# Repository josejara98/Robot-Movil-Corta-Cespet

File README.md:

# 🤖 Prototipo de Robot móvil Cortacésped

Este repositorio contiene el diseño de hardware y el firmware base para la unidad de control central de un robot móvil cortacésped teleoperado

El núcleo de este proyecto es una **PCB personalizada**  diseñada para gestionar potencia, navegación y sistema de seguridad utilizando el microcontrolador **ESP32-S3**.

## Especificaciones Técnicas de la PCB

Nuestra especialización se centra en la integración de sensores y la gestión de actuadores de potencia:

### Cerebro y Conectividad
* **MCU:** `ESP32-S3-WROOM-1`. Doble núcleo con soporte nativo para Wi-Fi y Bluetooth

### Sistema de Seguridad y Detección de Obstáculos
El robot implementa una estrategia de seguridad de dos niveles:
1.  **Nivel Preventivo (Ultrasonidos):** 3 sensores ultrasónicos estratégicamente posicionados para la detección de obstáculos a distancia
2.  **Nivel de Contacto (Bumpers):** 4 finales de carrera instalados en el chasis como "Bumpers". Funcionan como la última barrera física
* **Regulación:** `LDL1117S33R`. LDO de alta eficiencia para una alimentación estable de 3.3V.
* **Precisión de Batería:** `ADS1015LIDGSR`. ADC externo de 12 bits para un monitoreo crítico del voltaje

### Navegación y Movimiento
* **IMU:** `IIM-42652`. Sensor de 6 ejes de grado industrial para mantener el rumbo y detectar inclinaciones peligrosas.
* **Control de Tracción:** Pines de salida (Dupont) para conectar un **driver de motor DC externo** para el desplazamiento del robot.

### Sistema de Corte (Brushless)
La PCB cuenta con salidas específicas para controlar **3 ESC (Electronic Speed Controllers)** independientes:
* **2 Motores Brushless:** Dedicados al corte principal de césped.
* **1 Motor Brushless:** Dedicado a la función de bordeadora

### Interfaz de Usuario
* **Buzzer SMT:** `CMI-9705-0580-SMT-TR`. Notifica mediante códigos acústicos:
    * **Movimiento inminente:** Alerta antes de activar cuchillas o tracción.
    * **Batería Baja:** Alerta de retorno a base.

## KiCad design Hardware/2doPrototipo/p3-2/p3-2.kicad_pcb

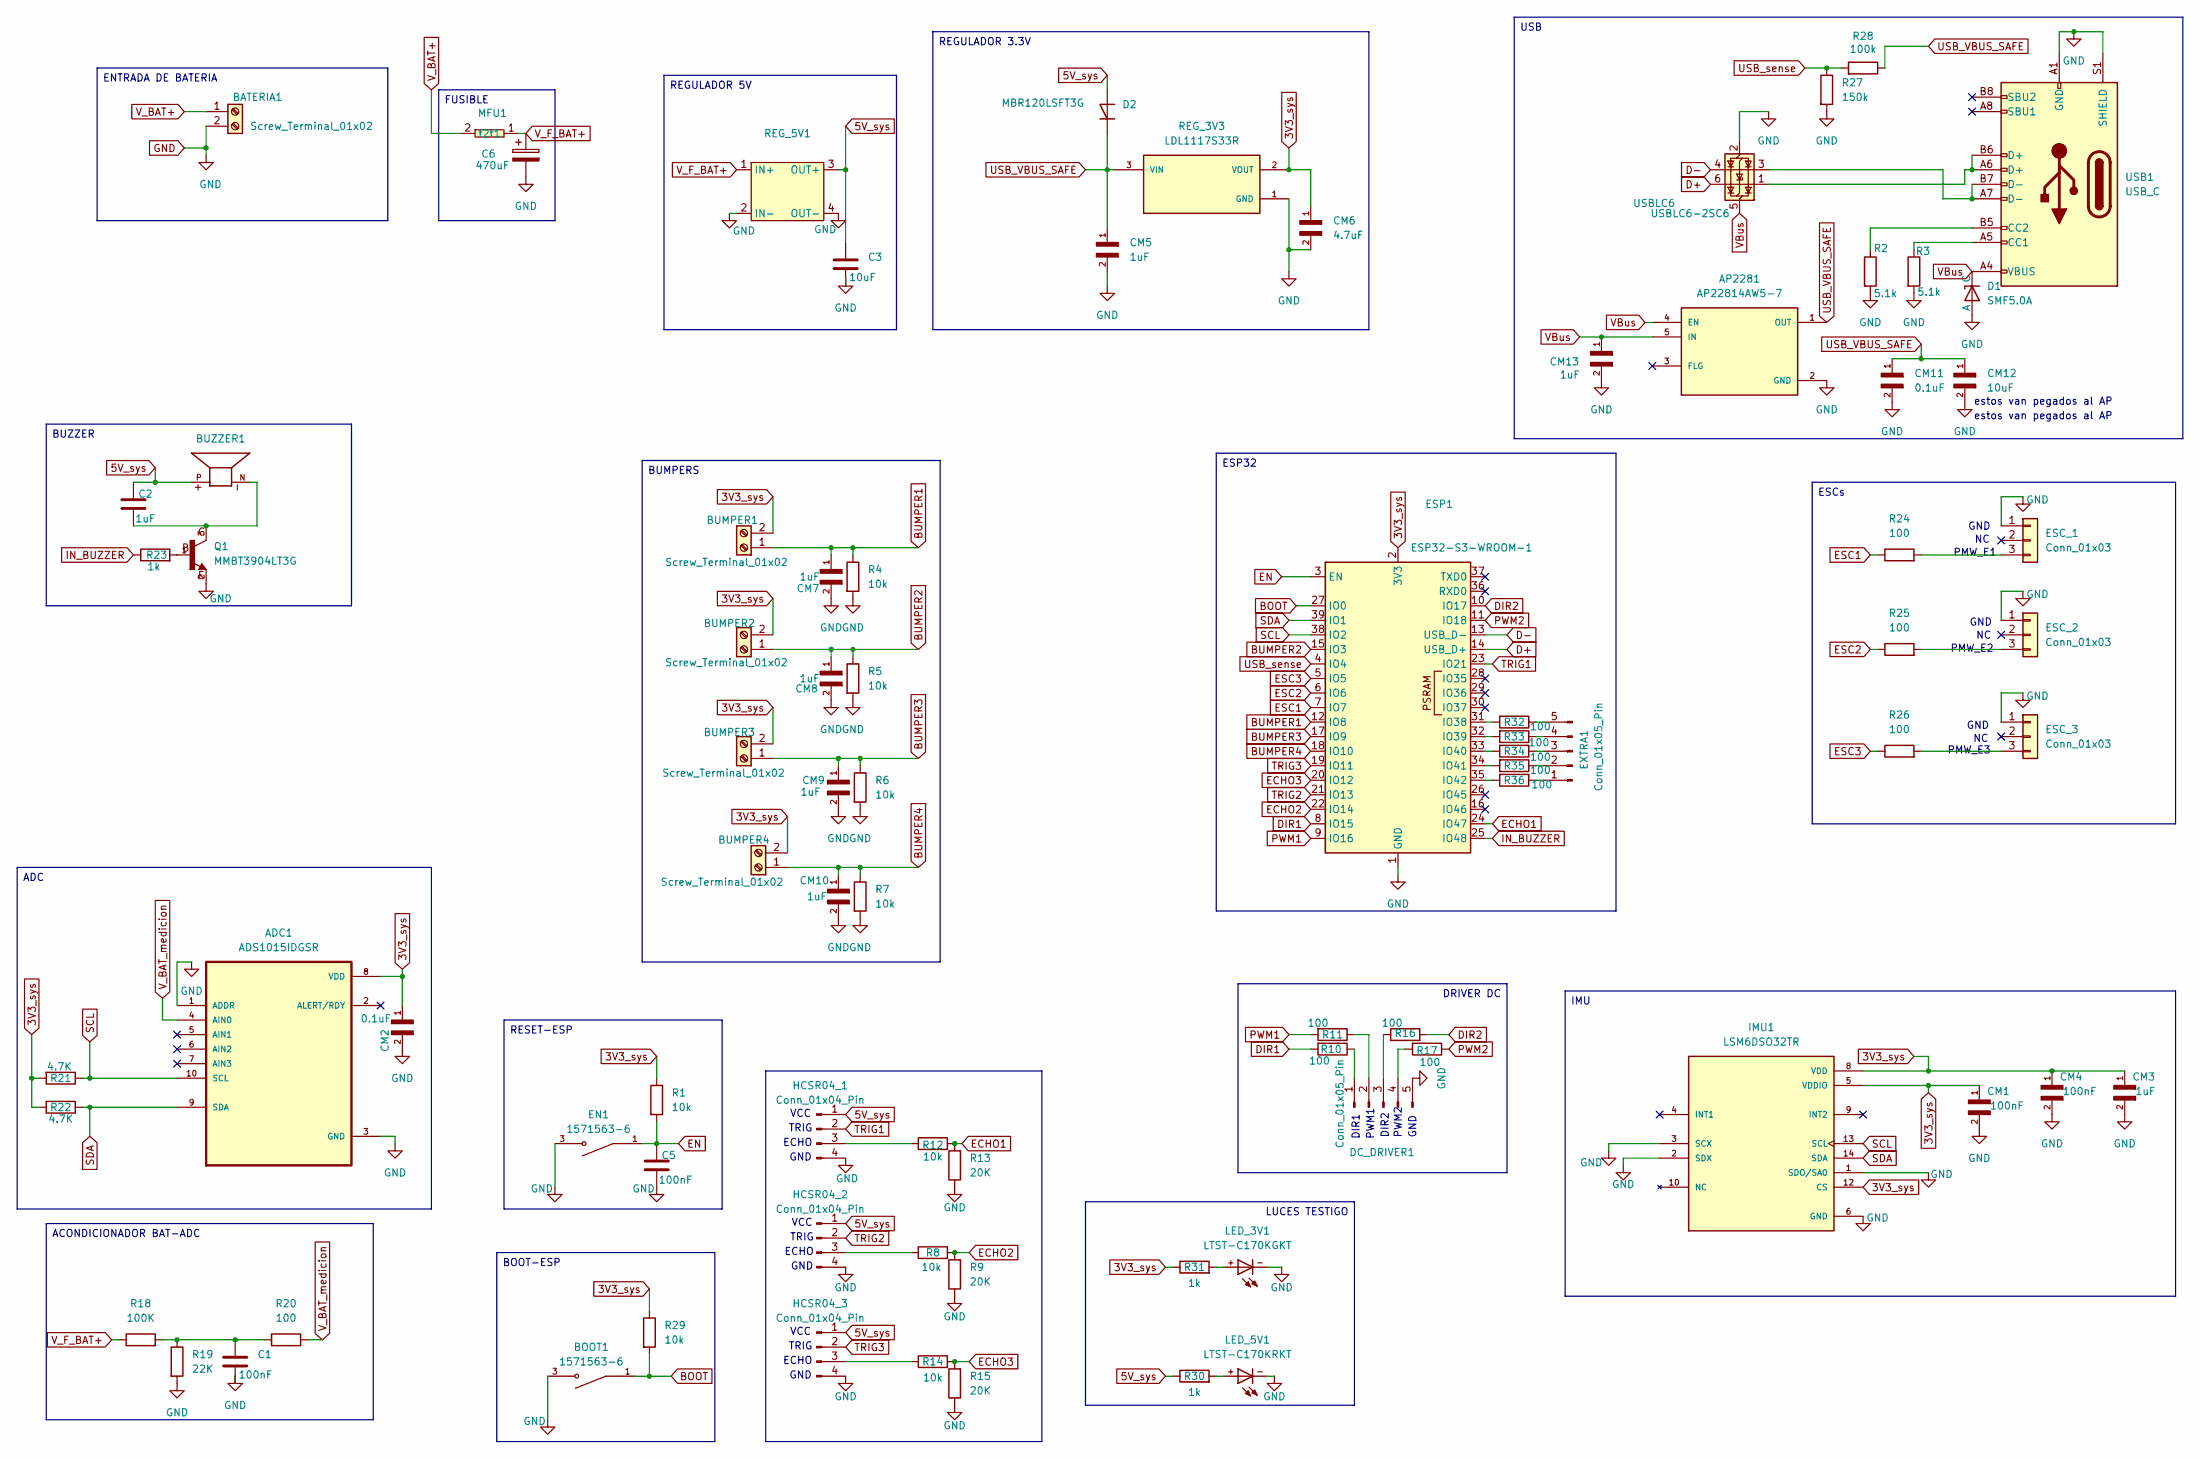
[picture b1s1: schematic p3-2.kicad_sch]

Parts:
ADC1: ADS1015IDGSR; SOP50P490X110-10N
AP2281: AP22814AW5-7; SOT95P285X140-5N; PARTREV 1
BATERIA1: Screw_Terminal_01x02; TerminalBlock_MetzConnect_Type055_RT01502HDWU_1x02_P5.00mm_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
BOOT1: 1571563-6; SW_1571563-6; PARTREV V
BUMPER1, BUMPER2, BUMPER3, BUMPER4: Screw_Terminal_01x02; TerminalBlock_Phoenix_MPT-0,5-2-2.54_1x02_P2.54mm_Horizontal
BUZZER1: CMI-9705-0580-SMT-TR; CUI_CMI-9705-0580-SMT-TR; PARTREV 1.0
C1, C5: 100nF; C_0805_2012Metric_Pad1.18x1.45mm_HandSolder
C2: 1uF; C_0805_2012Metric_Pad1.18x1.45mm_HandSolder
C3: 10uF; C_0805_2012Metric_Pad1.18x1.45mm_HandSolder
C6: 470uF; CP_Elec_10x10
CM1, CM4: 100nF; CAPC2012X140N; DigiKey_Part_Number 478-08056D104KAT2ACT-ND
CM2, CM11: 0.1uF; CAPC2012X140N; DigiKey_Part_Number 478-08056D104KAT2ACT-ND
CM3, CM5, CM7, CM8, CM9, CM10, CM13: 1uF; CAPC2012X140N; DigiKey_Part_Number 478-08056D104KAT2ACT-ND
CM6: 4.7uF; CAPC2012X140N; DigiKey_Part_Number 478-08056D104KAT2ACT-ND
CM12: 10uF; CAPC2012X140N; DigiKey_Part_Number 478-08056D104KAT2ACT-ND
D1: SMF5.0A; P37_SOD-123FL
D2: MBR120LSFT3G; D_SOD-123F
DC_DRIVER1: Conn_01x05_Pin; PinHeader_1x05_P2.54mm_Vertical
EN1: 1571563-6; SW_1571563-6; PARTREV V
ESC_1, ESC_2, ESC_3: Conn_01x03; PinHeader_1x03_P2.54mm_Vertical
ESP1: ESP32-S3-WROOM-1
EXTRA1: Conn_01x05_Pin; PinHeader_1x05_P2.54mm_Vertical
HCSR04_1, HCSR04_2, HCSR04_3: Conn_01x04_Pin; PinSocket_1x04_P2.54mm_Vertical
IMU1: LSM6DSO32TR; XDCR_LSM6DSO32TR; PARTREV 1
LED_3V1: LTST-C170KGKT; DIOC200X125X110
LED_5V1: LTST-C170KRKT; DIOC200X125X110
MFU1: MFU0805FF01000PW00
Q1: MMBT3904LT3G; SOT23; DigiKey_Part_Number MMBT3904LT3GOSCT-ND
R1, R4, R5, R6, R7, R8, R12, R14, R29: 10k; R_0805_2012Metric_Pad1.20x1.40mm_HandSolder
R2, R3: 5.1k; R_0805_2012Metric_Pad1.20x1.40mm_HandSolder
R9, R13, R15: 20K; R_0805_2012Metric_Pad1.20x1.40mm_HandSolder
R10, R11, R16, R17, R20, R24, R25, R26, R32, R33, R34, R35, R36: 100; R_0805_2012Metric_Pad1.20x1.40mm_HandSolder
R18: 100K; R_0805_2012Metric_Pad1.20x1.40mm_HandSolder
R19: 22K; R_0805_2012Metric_Pad1.20x1.40mm_HandSolder
R21, R22: 4.7K; R_0805_2012Metric_Pad1.20x1.40mm_HandSolder
R23, R30, R31: 1k; R_0805_2012Metric_Pad1.20x1.40mm_HandSolder
R27: 150k; R_0805_2012Metric_Pad1.20x1.40mm_HandSolder
R28: 100k; R_0805_2012Metric_Pad1.20x1.40mm_HandSolder
REG_3V3: LDL1117S33R; SOT230P700X180-4N; PARTREV 7
REG_5V1: MINI590
USB1: USB_C; USB_C_Receptacle_GCT_USB4105-xx-A_16P_TopMnt_Horizontal
USBLC6: USBLC6-2SC6; SOT-23-6

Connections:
3V3_sys: ADC1.8 (VDD), BUMPER1.2, BUMPER2.2, BUMPER3.2, BUMPER4.2, CM1.1, CM2.1, CM3.1, CM4.1, CM6.1, ESP1.2 (3V3), IMU1.5 (VDDIO), IMU1.8 (VDD), IMU1.12 (CS), R1.1, R21.2, R22.2, R29.1, R31.1, REG_3V3.2 (VOUT), REG_3V3.4 (VOUT)
5V_sys: BUZZER1.P, C2.1, C3.1, D2.2 (A), HCSR04_1.1, HCSR04_2.1, HCSR04_3.1, R30.1, REG_5V1.3 (OUT+)
BOOT: BOOT1.1, BOOT1.2, ESP1.27 (IO0), R29.2
BUMPER1: BUMPER1.1, CM7.1, ESP1.12 (IO8), R4.1
BUMPER2: BUMPER2.1, CM8.1, ESP1.15 (IO3), R5.1
BUMPER3: BUMPER3.1, CM9.1, ESP1.17 (IO9), R6.1
BUMPER4: BUMPER4.1, CM10.1, ESP1.18 (IO10), R7.1
D+: ESP1.14 (USB_D+), USBLC6.6 (I/O1)
D-: ESP1.13 (USB_D-), USBLC6.4 (I/O2)
DIR1: ESP1.8 (IO15), R10.2
DIR2: ESP1.10 (IO17), R16.2
ECHO1: ESP1.24 (IO47), R12.2, R13.2
ECHO2: ESP1.22 (IO14), R8.2, R9.2
ECHO3: ESP1.20 (IO12), R14.2, R15.2
EN: C5.1, EN1.1, EN1.2, ESP1.3 (EN), R1.2
ESC1: ESP1.7 (IO7), R24.1
ESC2: ESP1.6 (IO6), R25.1
ESC3: ESP1.5 (IO5), R26.1
GND: ADC1.1 (ADDR), ADC1.3 (GND), AP2281.2 (GND), BATERIA1.2, BOOT1.3, BOOT1.4, C1.2, C3.2, C5.2, C6.2, CM1.2, CM2.2, CM3.2, CM4.2, CM5.2, CM6.2, CM7.2, CM8.2, CM9.2, CM10.2, CM11.2, CM12.2, CM13.2, D1.2 (A), DC_DRIVER1.5, EN1.3, EN1.4, ESC_1.1, ESC_2.1, ESC_3.1, ESP1.1 (GND), ESP1.40 (GND), ESP1.41 (GND), HCSR04_1.4, HCSR04_2.4, HCSR04_3.4, IMU1.1 (SDO/SA0), IMU1.2 (SDX), IMU1.3 (SCX), IMU1.6 (GND), IMU1.7 (GND), LED_3V1.-, LED_5V1.-, Q1.2, R2.2, R3.2, R4.2, R5.2, R6.2, R7.2, R9.1, R13.1, R15.1, R19.2, R27.2, REG_3V3.1 (GND), REG_5V1.2 (IN-), REG_5V1.4 (OUT-), USB1.A1 (GND), USB1.A12 (GND), USB1.B1 (GND), USB1.B12 (GND), USB1.S1 (SHIELD), USBLC6.2 (GND); also elsewhere on the board
IN_BUZZER: ESP1.25 (IO48), R23.1
unnamed: BUZZER1.N, C2.2, Q1.3
unnamed: C1.1, R18.2, R19.1, R20.1
unnamed: DC_DRIVER1.1, R10.1
unnamed: DC_DRIVER1.2, R11.1
unnamed: DC_DRIVER1.3, R16.1
unnamed: DC_DRIVER1.4, R17.2
unnamed: ESC_1.3, R24.2
unnamed: ESC_2.3, R25.2
unnamed: ESC_3.3, R26.2
unnamed: ESP1.31 (IO38), R32.2
unnamed: ESP1.32 (IO39), R33.2
unnamed: ESP1.33 (IO40), R34.2
unnamed: ESP1.34 (IO41), R35.2
unnamed: ESP1.35 (IO42), R36.2
unnamed: EXTRA1.1, R36.1
unnamed: EXTRA1.2, R35.1
unnamed: EXTRA1.3, R34.1
unnamed: EXTRA1.4, R33.1
unnamed: EXTRA1.5, R32.1
unnamed: HCSR04_1.3, R12.1
unnamed: HCSR04_2.3, R8.1
unnamed: HCSR04_3.3, R14.1
unnamed: LED_3V1.+, R31.2
unnamed: LED_5V1.+, R30.2
unnamed: Q1.1, R23.2
unnamed: R3.1, USB1.A5 (CC1)
unnamed: R2.1, USB1.B5 (CC2)
unnamed: USB1.A6 (D+), USB1.B6 (D+), USBLC6.1 (I/O1)
unnamed: USB1.A7 (D-), USB1.B7 (D-), USBLC6.3 (I/O2)
PWM1: ESP1.9 (IO16), R11.2
PWM2: ESP1.11 (IO18), R17.1
SCL: ADC1.10 (SCL), ESP1.38 (IO2), IMU1.13 (SCL), R21.1
SDA: ADC1.9 (SDA), ESP1.39 (IO1), IMU1.14 (SDA), R22.1
TRIG1: ESP1.23 (IO21), HCSR04_1.2
TRIG2: ESP1.21 (IO13), HCSR04_2.2
TRIG3: ESP1.19 (IO11), HCSR04_3.2
USB_VBUS_SAFE: AP2281.1 (OUT), CM5.1, CM11.1, CM12.1, D2.1 (K), R28.1, REG_3V3.3 (VIN)
USB_sense: ESP1.4 (IO4), R27.1, R28.2
VBus: AP2281.4 (EN), AP2281.5 (IN), CM13.1, D1.1 (C), USB1.A4 (VBUS), USB1.A9 (VBUS), USB1.B4 (VBUS), USB1.B9 (VBUS), USBLC6.5 (VBUS)
V_BAT+: BATERIA1.1, MFU1.2 (f2)
V_BAT_medicion: ADC1.4 (AIN0), R20.2
V_F_BAT+: C6.1, MFU1.1 (f1), R18.1, REG_5V1.1 (IN+)

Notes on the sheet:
TRIG
PWM2
GND
estos van pegados al AP
VCC
GND
ECHO
PMW_E2
PMW_E3
DIR2
DIR1
PWM1
PMW_E1
ADC
REGULADOR 3.3V
RESET-ESP
ENTRADA DE BATERIA
DRIVER DC
BUMPERS
BUZZER
BOOT-ESP
ESP32
LUCES TESTIGO
ESCs
ACONDICIONADOR BAT-ADC
USB
REGULADOR 5V
IMU
FUSIBLE

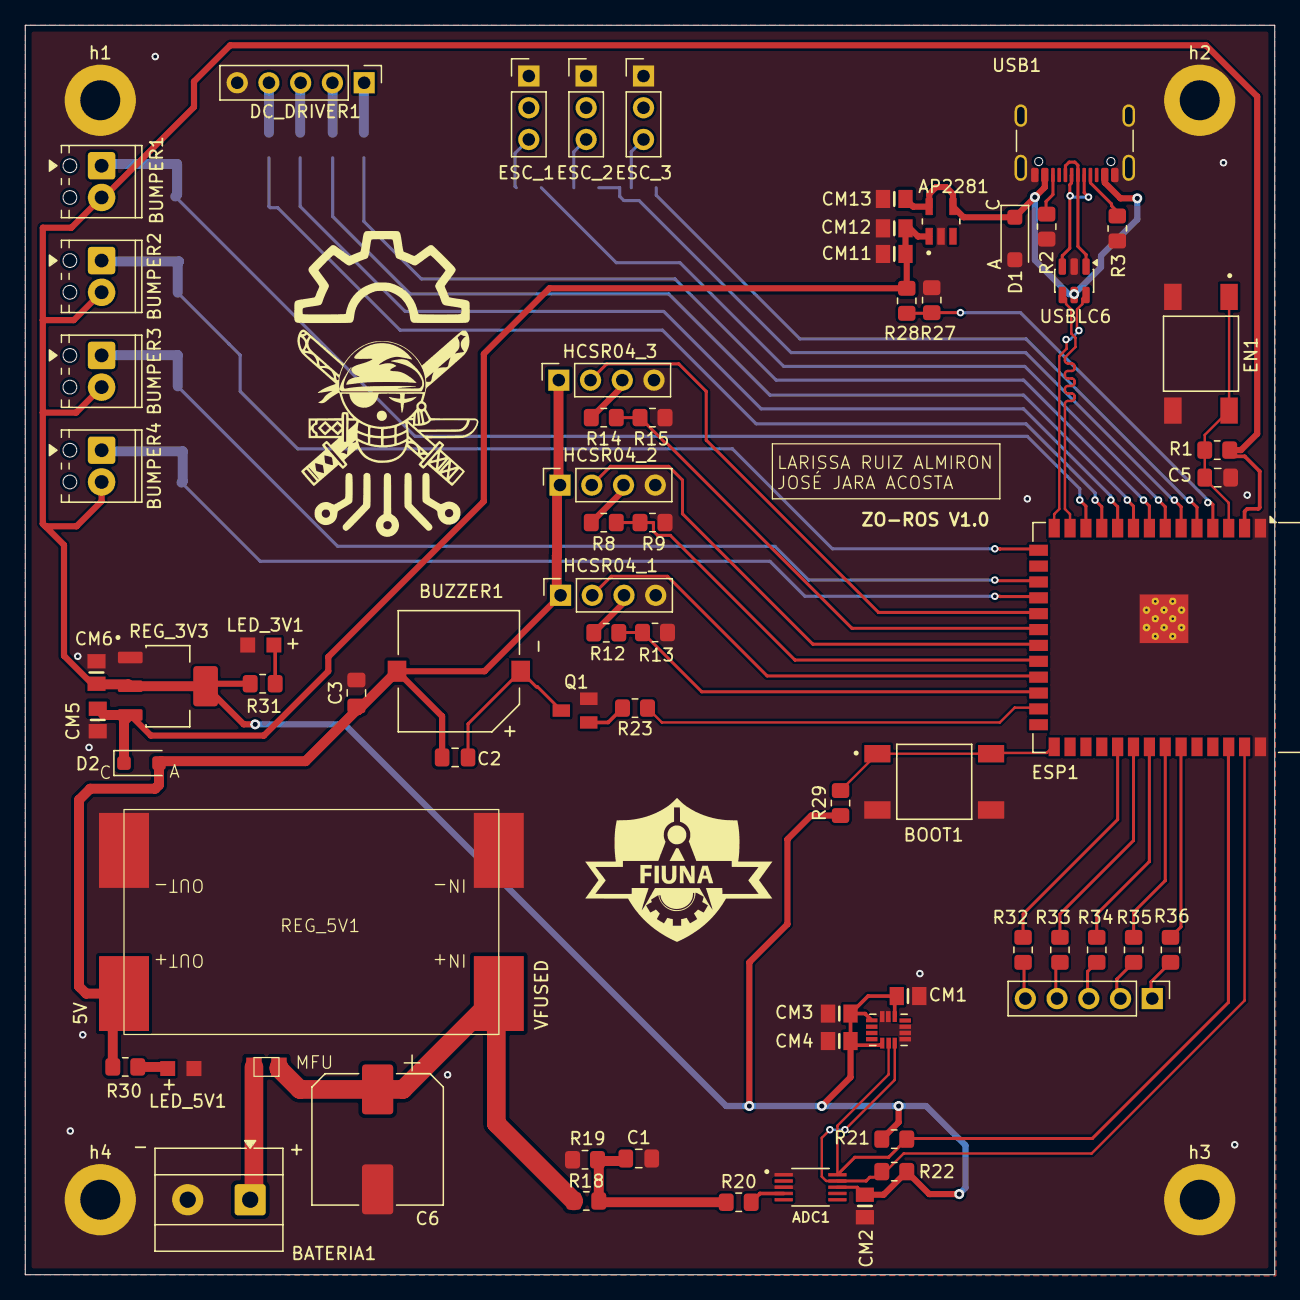
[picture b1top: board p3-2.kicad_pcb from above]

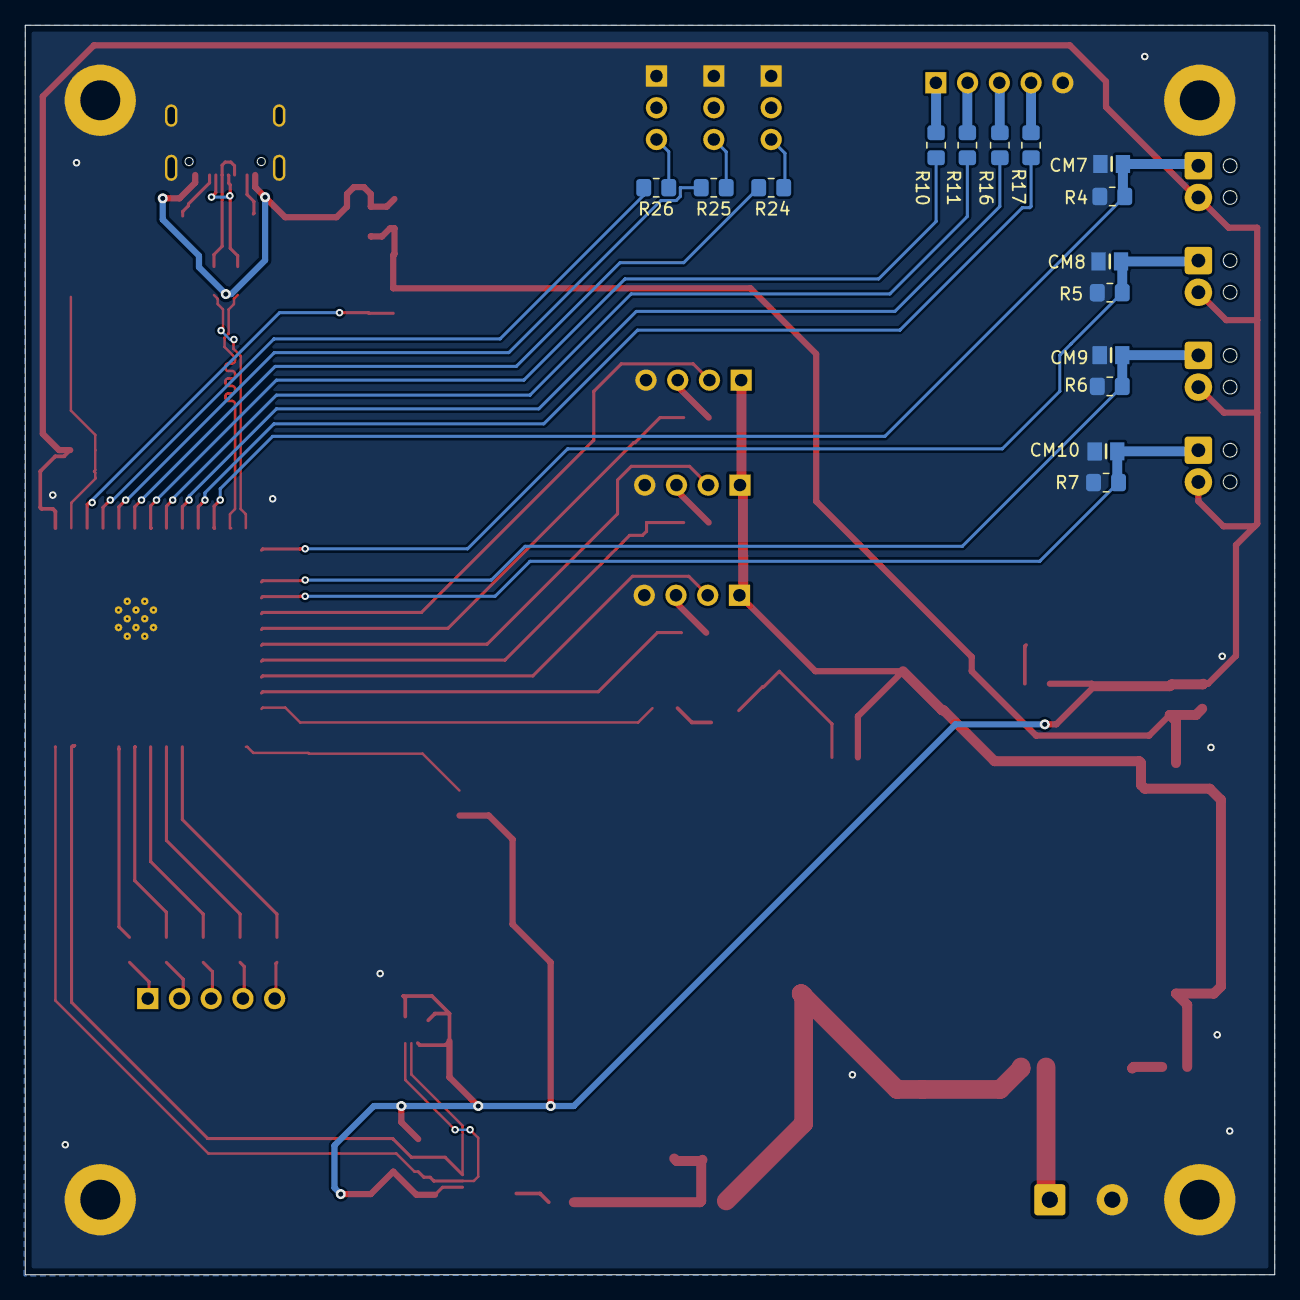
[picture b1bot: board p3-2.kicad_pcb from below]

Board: 2 copper layers, 100.0 x 100.0 mm, 90 parts (15 on the bottom side), 62 nets.

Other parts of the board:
FIUNA: LOGO; logo
ZORO: LOGO; zoro
h1, h2, h3, h4: MountingHole_3.2mm_M3_ISO7380_Pad

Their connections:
GND: h1.1, h2.2, h3.3, h4.4; also elsewhere on the board

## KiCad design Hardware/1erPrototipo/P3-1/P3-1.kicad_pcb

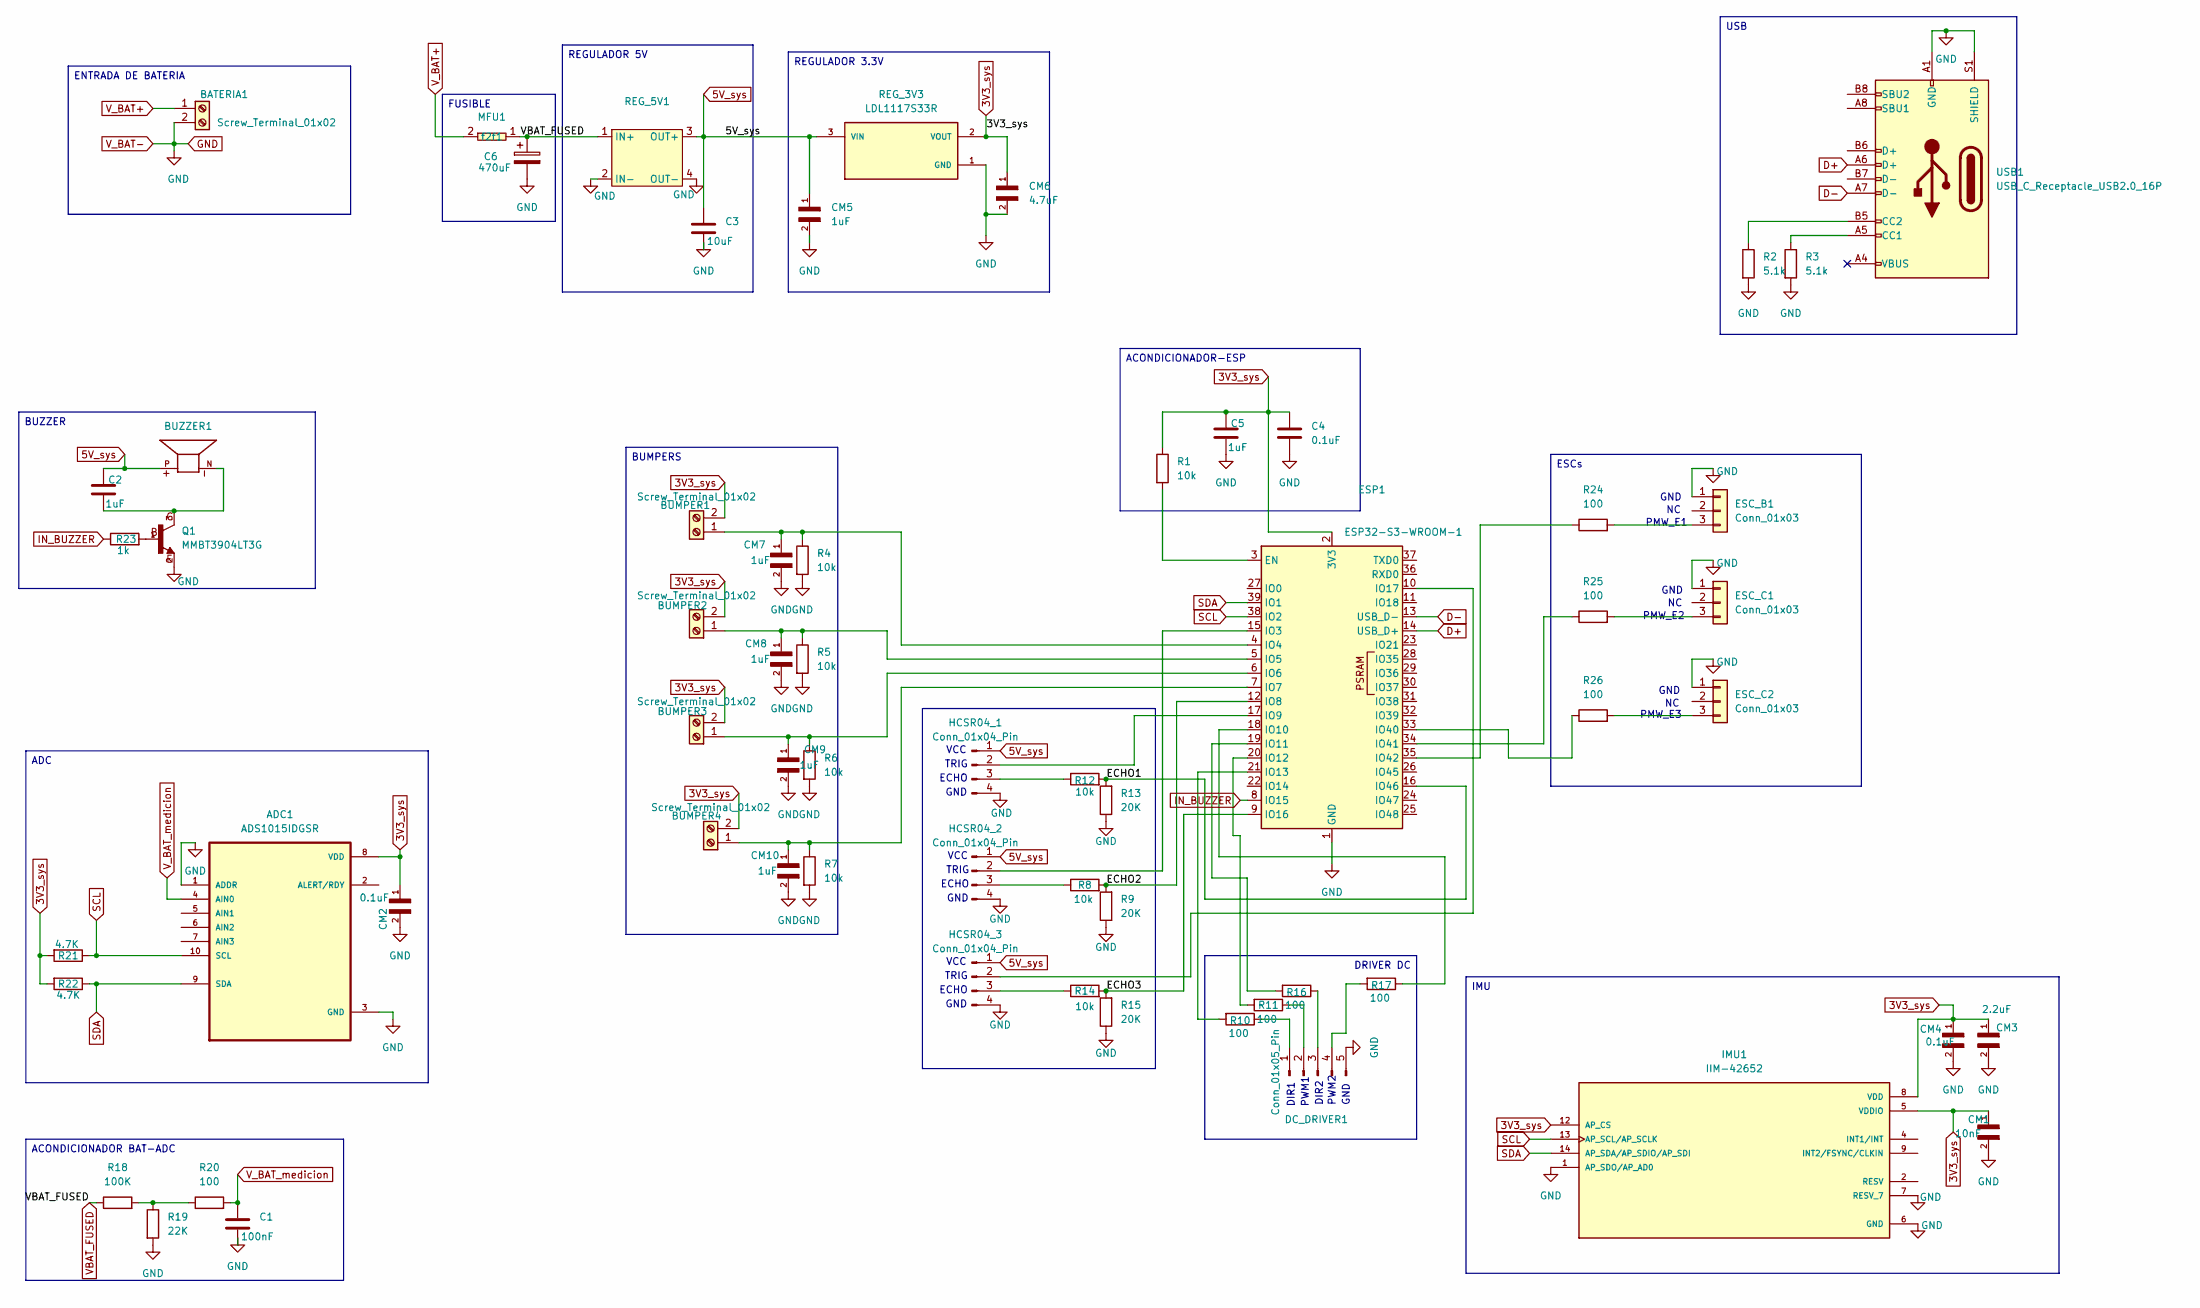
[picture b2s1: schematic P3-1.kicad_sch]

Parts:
ADC1: ADS1015IDGSR; SOP50P490X110-10N
BATERIA1: Screw_Terminal_01x02; TerminalBlock_MetzConnect_Type055_RT01502HDWU_1x02_P5.00mm_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
BUMPER1, BUMPER2, BUMPER3, BUMPER4: Screw_Terminal_01x02; TerminalBlock_Phoenix_MPT-0,5-2-2.54_1x02_P2.54mm_Horizontal
BUZZER1: CMI-9705-0580-SMT-TR; CUI_CMI-9705-0580-SMT-TR; PARTREV 1.0
C1: 100nF; C_0805_2012Metric_Pad1.18x1.45mm_HandSolder
C2, C5: 1uF; C_0805_2012Metric_Pad1.18x1.45mm_HandSolder
C3: 10uF; C_0805_2012Metric_Pad1.18x1.45mm_HandSolder
C4: 0.1uF; C_0805_2012Metric_Pad1.18x1.45mm_HandSolder
C6: 470uF; CP_Elec_10x10
CM1: 10nF; CAPC2012X140N; DigiKey_Part_Number 478-08056D104KAT2ACT-ND
CM2, CM4: 0.1uF; CAPC2012X140N; DigiKey_Part_Number 478-08056D104KAT2ACT-ND
CM3: 2.2uF; CAPC2012X140N; DigiKey_Part_Number 478-08056D104KAT2ACT-ND
CM5, CM7, CM8, CM9, CM10: 1uF; CAPC2012X140N; DigiKey_Part_Number 478-08056D104KAT2ACT-ND
CM6: 4.7uF; CAPC2012X140N; DigiKey_Part_Number 478-08056D104KAT2ACT-ND
DC_DRIVER1: Conn_01x05_Pin; PinHeader_1x05_P2.54mm_Vertical
ESC_B1: Conn_01x03; PinHeader_1x03_P2.54mm_Vertical
ESC_C1, ESC_C2: Conn_01x03; PinHeader_1x03_P2.54mm_Vertical
ESP1: ESP32-S3-WROOM-1
HCSR04_1, HCSR04_2, HCSR04_3: Conn_01x04_Pin; PinSocket_1x04_P2.54mm_Vertical
IMU1: IIM-42652; PQFN50P250X300X97-14N; PARTREV 1.0
MFU1: MFU0603FF01000PW00
Q1: MMBT3904LT3G; SOT23; DigiKey_Part_Number MMBT3904LT3GOSCT-ND
R1, R4, R5, R6, R7, R8, R12, R14: 10k; R_0805_2012Metric_Pad1.20x1.40mm_HandSolder
R2, R3: 5.1k; R_0805_2012Metric_Pad1.20x1.40mm_HandSolder
R9, R13, R15: 20K; R_0805_2012Metric_Pad1.20x1.40mm_HandSolder
R10, R11, R16, R17, R20, R24, R25, R26: 100; R_0805_2012Metric_Pad1.20x1.40mm_HandSolder
R18: 100K; R_0805_2012Metric_Pad1.20x1.40mm_HandSolder
R19: 22K; R_0805_2012Metric_Pad1.20x1.40mm_HandSolder
R21, R22: 4.7K; R_0805_2012Metric_Pad1.20x1.40mm_HandSolder
R23: 1k; R_0805_2012Metric_Pad1.20x1.40mm_HandSolder
REG_3V3: LDL1117S33R; SOT230P700X180-4N; PARTREV 7
REG_5V1: MINI590
USB1: USB_C_Receptacle_USB2.0_16P; USB_C_Receptacle_GCT_USB4105-xx-A_16P_TopMnt_Horizontal

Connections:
3V3_sys: ADC1.8 (VDD), BUMPER1.2, BUMPER2.2, BUMPER3.2, BUMPER4.2, C4.1, C5.1, CM1.1, CM2.1, CM3.1, CM4.1, CM6.1, ESP1.2 (3V3), IMU1.5 (VDDIO), IMU1.8 (VDD), IMU1.12 (AP_CS), R1.1, R21.2, R22.2, REG_3V3.2 (VOUT), REG_3V3.4 (VOUT)
5V_sys: BUZZER1.P, C2.1, C3.1, CM5.1, HCSR04_1.1, HCSR04_2.1, HCSR04_3.1, REG_3V3.3 (VIN), REG_5V1.3 (OUT+)
/ECHO1: ESP1.16 (IO46), R12.2, R13.2
/ECHO2: ESP1.12 (IO8), R8.2, R9.2
/ECHO3: ESP1.9 (IO16), R14.2, R15.2
D+: ESP1.14 (USB_D+), USB1.A6 (D+)
D-: ESP1.13 (USB_D-), USB1.A7 (D-)
GND: ADC1.1 (ADDR), ADC1.3 (GND), BATERIA1.2, C1.2, C3.2, C4.2, C5.2, C6.2, CM1.2, CM2.2, CM3.2, CM4.2, CM5.2, CM6.2, CM7.2, CM8.2, CM9.2, CM10.2, DC_DRIVER1.5, ESC_B1.1, ESC_C1.1, ESC_C2.1, ESP1.1 (GND), ESP1.40 (GND), ESP1.41 (GND), HCSR04_1.4, HCSR04_2.4, HCSR04_3.4, IMU1.1 (AP_SDO/AP_AD0), IMU1.6 (GND), IMU1.7 (RESV_7), Q1.2, R2.2, R3.2, R4.2, R5.2, R6.2, R7.2, R9.1, R13.1, R15.1, R19.2, REG_3V3.1 (GND), REG_5V1.2 (IN-), REG_5V1.4 (OUT-), USB1.A1 (GND), USB1.A12 (GND), USB1.B1 (GND), USB1.B12 (GND), USB1.S1 (SHIELD)
IN_BUZZER: ESP1.8 (IO15), R23.1
unnamed: BUMPER1.1, CM7.1, ESP1.4 (IO4), R4.1
unnamed: BUMPER2.1, CM8.1, ESP1.5 (IO5), R5.1
unnamed: BUMPER3.1, CM9.1, ESP1.6 (IO6), R6.1
unnamed: BUMPER4.1, CM10.1, ESP1.7 (IO7), R7.1
unnamed: BUZZER1.N, C2.2, Q1.3
unnamed: DC_DRIVER1.1, R10.1
unnamed: DC_DRIVER1.2, R11.1
unnamed: DC_DRIVER1.3, R16.1
unnamed: DC_DRIVER1.4, R17.2
unnamed: ESC_B1.3, R24.2
unnamed: ESC_C1.3, R25.2
unnamed: ESC_C2.3, R26.2
unnamed: ESP1.3 (EN), R1.2
unnamed: ESP1.15 (IO3), HCSR04_2.2
unnamed: ESP1.17 (IO9), HCSR04_1.2
unnamed: ESP1.18 (IO10), R17.1
unnamed: ESP1.19 (IO11), R16.2
unnamed: ESP1.20 (IO12), R11.2
unnamed: ESP1.21 (IO13), R10.2
unnamed: ESP1.10 (IO17), HCSR04_3.2
unnamed: ESP1.33 (IO40), R26.1
unnamed: ESP1.34 (IO41), R25.1
unnamed: ESP1.35 (IO42), R24.1
unnamed: HCSR04_1.3, R12.1
unnamed: HCSR04_2.3, R8.1
unnamed: HCSR04_3.3, R14.1
unnamed: IMU1.2 (RESV), IMU1.3 (RESV), IMU1.10 (RESV), IMU1.11 (RESV)
unnamed: Q1.1, R23.2
unnamed: R18.2, R19.1, R20.1
unnamed: R3.1, USB1.A5 (CC1)
unnamed: R2.1, USB1.B5 (CC2)
SCL: ADC1.10 (SCL), ESP1.38 (IO2), IMU1.13 (AP_SCL/AP_SCLK), R21.1
SDA: ADC1.9 (SDA), ESP1.39 (IO1), IMU1.14 (AP_SDA/AP_SDIO/AP_SDI), R22.1
VBAT_FUSED: C6.1, MFU1.1 (f1), R18.1, REG_5V1.1 (IN+)
V_BAT+: BATERIA1.1, MFU1.2 (f2)
V_BAT_medicion: ADC1.4 (AIN0), C1.1, R20.2

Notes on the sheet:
TRIG
PWM2
GND
VCC
GND
ECHO
PMW_E2
PMW_E3
DIR2
DIR1
PWM1
PMW_E1
ADC
REGULADOR 3.3V
ENTRADA DE BATERIA
DRIVER DC
ACONDICIONADOR-ESP
BUMPERS
BUZZER
REGULADOR 5V
ESCs
ACONDICIONADOR BAT-ADC
USB
IMU
FUSIBLE

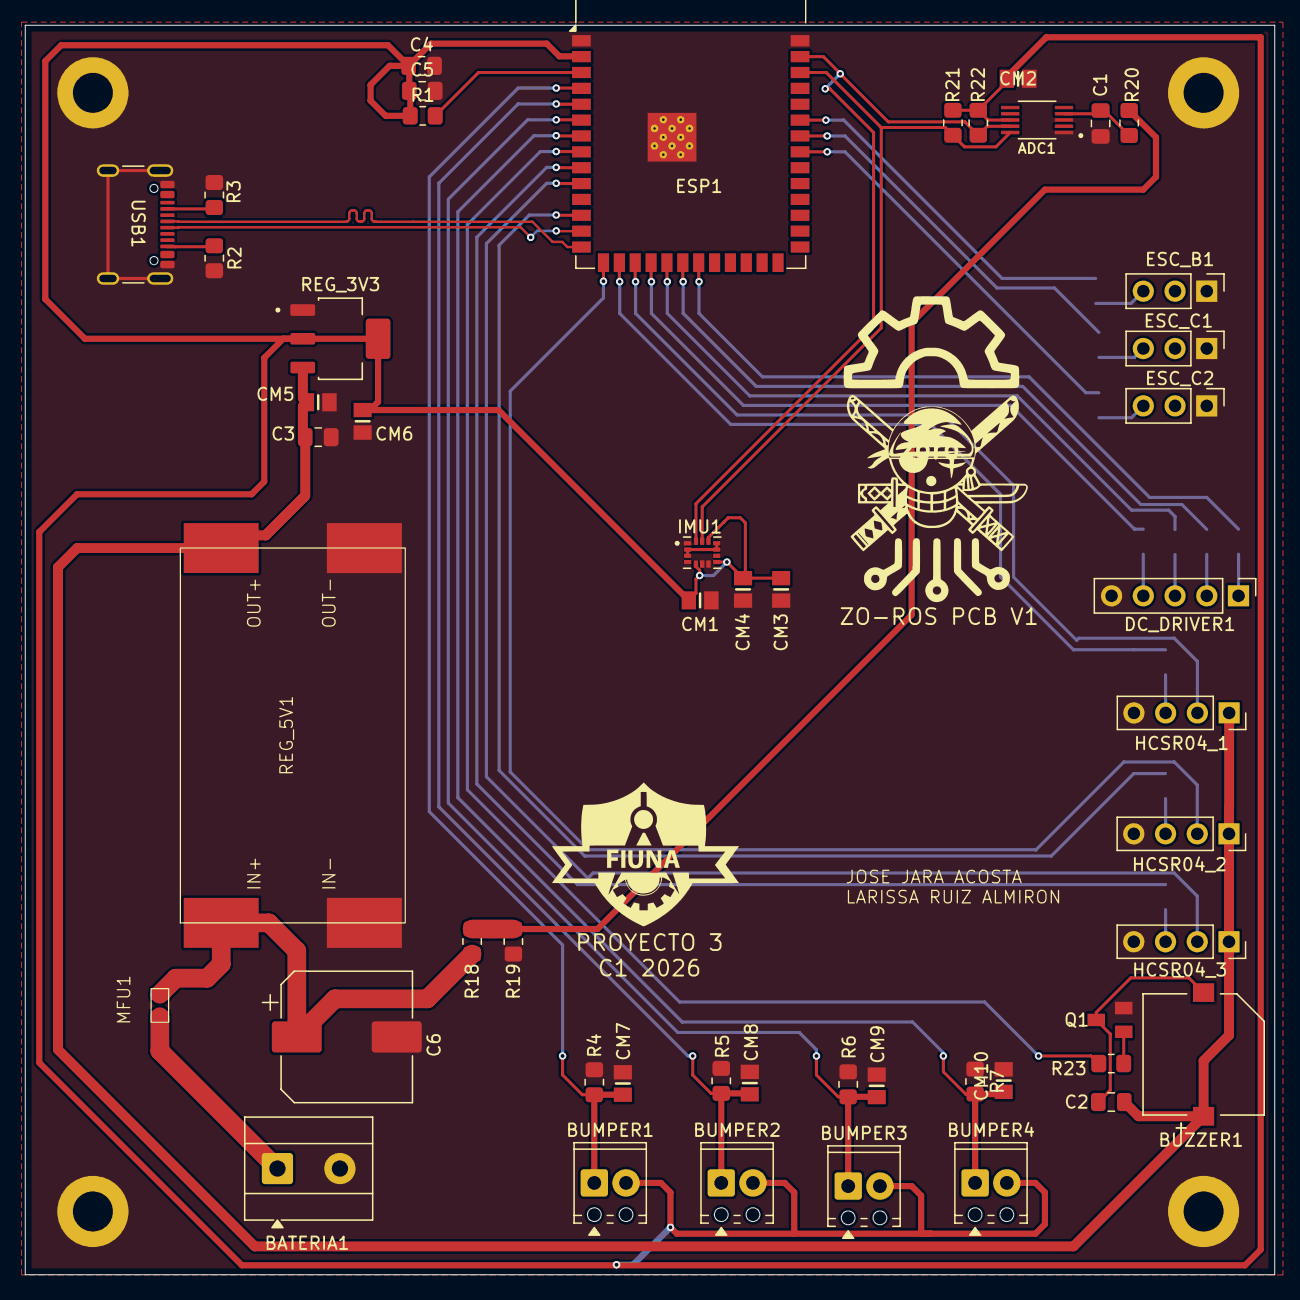
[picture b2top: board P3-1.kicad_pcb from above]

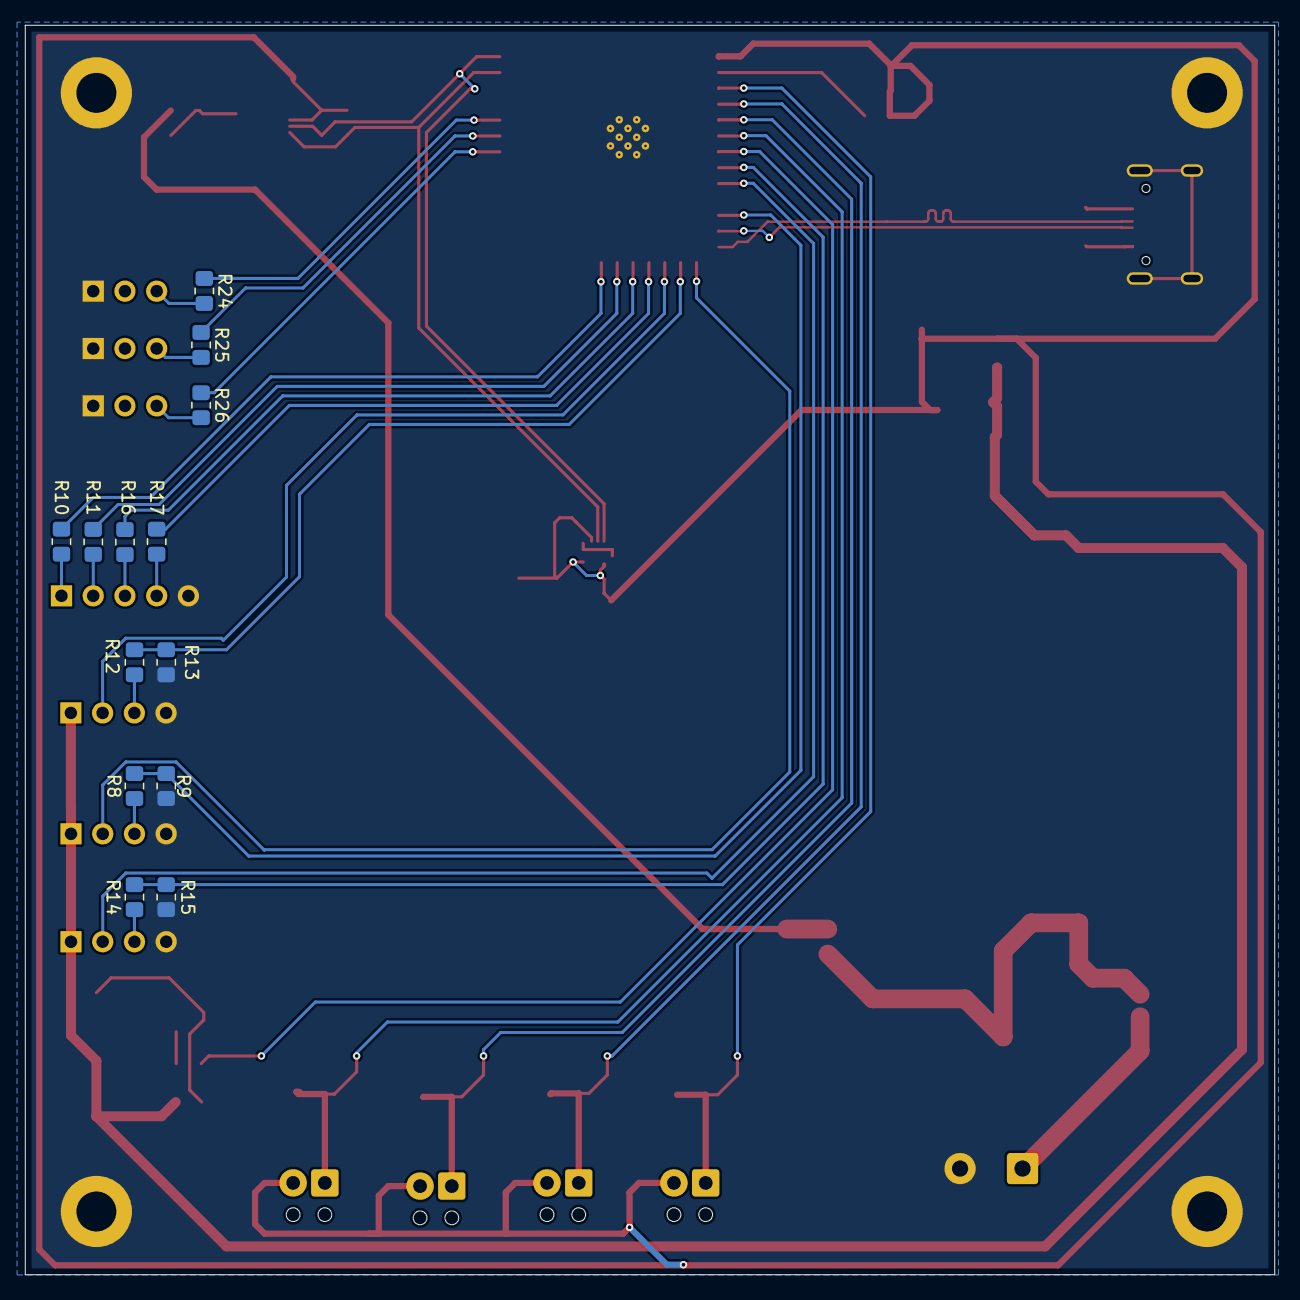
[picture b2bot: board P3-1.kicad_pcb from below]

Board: 2 copper layers, 100.0 x 100.0 mm, 64 parts (13 on the bottom side), 45 nets.

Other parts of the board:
zoro: LOGO; zoro

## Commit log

2026-03-29 Create Software
2026-03-29 Rename Software to Informe-P3-avance
2026-03-29 Librerias
2026-03-29 Datasheets
2026-03-29 Create s
2026-03-29 Create demo
2026-03-29 Rename Informe-P3-avance to Enlaces_utilizados
2026-03-29 Rename Enlaces_utilizados to links
2026-03-29 README.md
